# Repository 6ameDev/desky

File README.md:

# desky

Domain-driven monorepo: microcontroller firmware, future cross-platform
client, and shared protocol contracts.

## Repository structure

```plaintext
/
├── .github/              # CI/CD workflows
├── shared/
│   └── protocol/         # Machine-readable contracts, packet schemas, byte maps
├── embedded/             # C++ PlatformIO microcontroller firmware
│   ├── docs/             # documentation & architecture (untracked, owner-managed)
│   ├── scripts/          # UDP drive/telemetry peers (untracked, owner-managed)
│   ├── include/
│   ├── lib/
│   ├── src/
│   ├── test/
│   ├── Makefile
│   └── platformio.ini
├── client/               # Empty placeholder for future KMP / Compose project
├── .gitignore
├── AGENTS.md
└── README.md
```

## Firmware (PlatformIO)

All PlatformIO commands run inside `./embedded`:

```bash
cd embedded && pio run                 # verify compilation (dev)
cd embedded && pio run -e desky-release
cd embedded && pio test -e native-test # host Unity tests, no hardware
```

Prefer `make` targets (they encode the lessons) from the same directory:

```bash
cd embedded && make check        # gate: format + pins + both builds + host tests
cd embedded && make build
cd embedded && make test
cd embedded && make upload-monitor
```

Home WiFi setup (robot joins the home router so the laptop keeps internet):

```bash
cp embedded/.env.example embedded/.env   # fill in DESKY_LINK_SECRET only
```

Flash any firmware, boot with the head linked, then join the robot AP and
store the home credentials in the captive portal. No compiled WiFi secrets.

## Protocol contracts

See `shared/protocol/README.md` for the binary UDP packet layout
(6-byte control, 9-byte telemetry, big-endian, XOR checksum).
Normative source: `embedded/src/middleware/udp_codec.h`.

## Docs

Start at `embedded/docs/architecture/v2.md`, then `AGENTS.md`.
Serial/crash workflow: `embedded/docs/debugging.md`.

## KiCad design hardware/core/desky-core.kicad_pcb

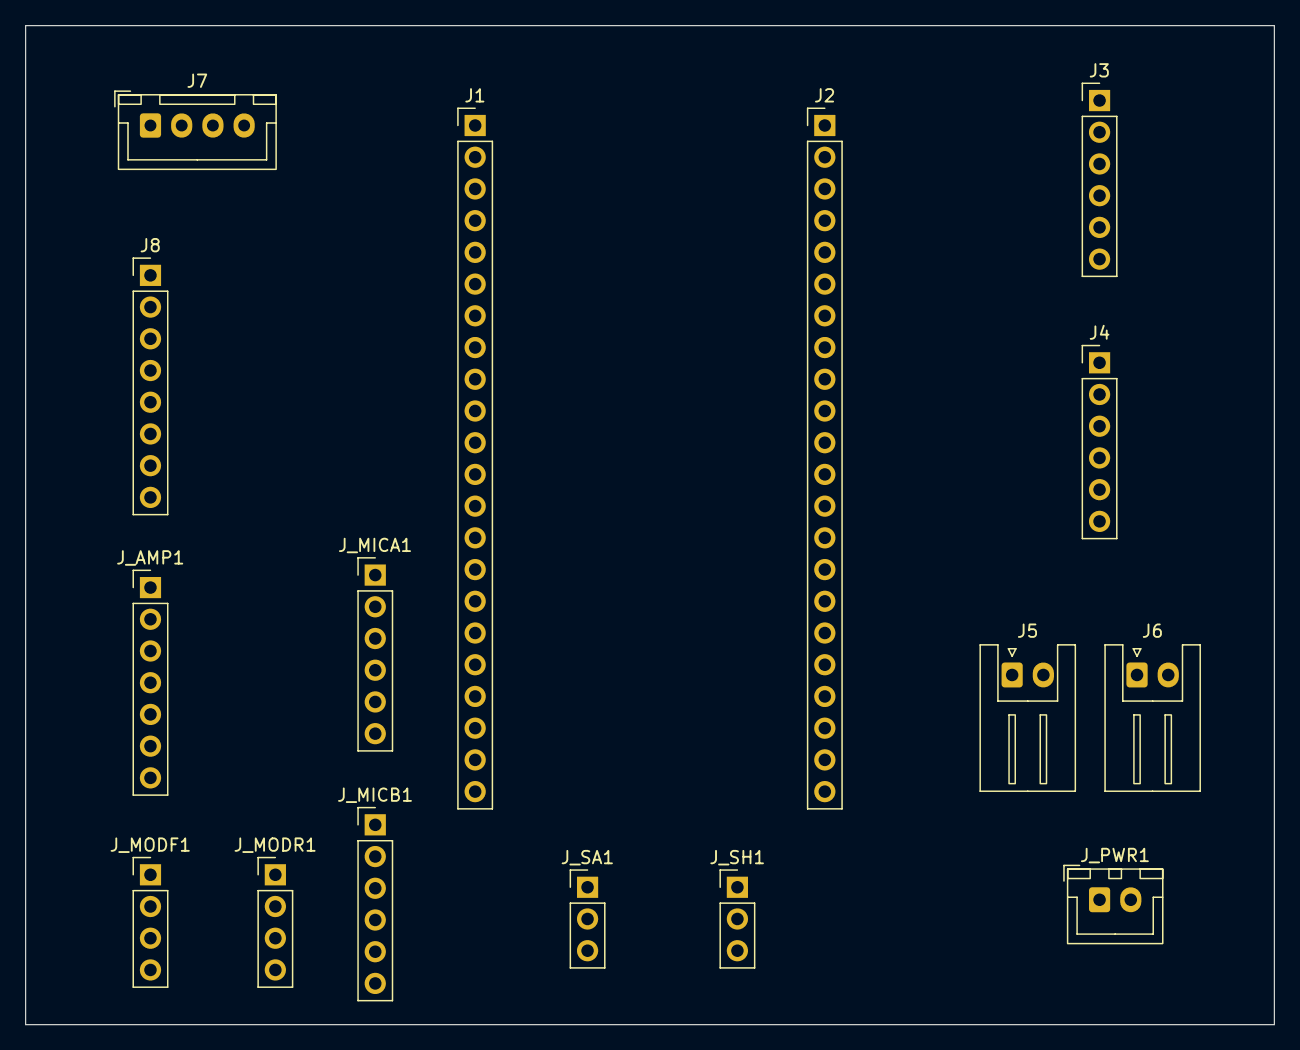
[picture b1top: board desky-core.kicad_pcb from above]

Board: 2 copper layers, 100.0 x 80.0 mm, 16 parts (0 on the bottom side), 24 nets, no tracks yet.

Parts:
J1: S3-LEFT; PinHeader_1x22_P2.54mm_Vertical
J2: S3-RIGHT; PinHeader_1x22_P2.54mm_Vertical
J3: DRV-LOGIC; PinHeader_1x06_P2.54mm_Vertical
J4: DRV-MOTOR; PinHeader_1x06_P2.54mm_Vertical
J5: MOT-L; JST_XH_S2B-XH-A_1x02_P2.50mm_Horizontal
J6: MOT-R; JST_XH_S2B-XH-A_1x02_P2.50mm_Horizontal
J7: TOF-VL53L0X; JST_XH_B4B-XH-A_1x04_P2.50mm_Vertical
J8: MPU-6500; PinHeader_1x08_P2.54mm_Vertical
J_AMP1: AMP-MAX98357A; PinHeader_1x07_P2.54mm_Vertical
J_MICA1: MIC-L; PinHeader_1x06_P2.54mm_Vertical
J_MICB1: MIC-R; PinHeader_1x06_P2.54mm_Vertical
J_MODF1: MOD-FWD-RCPT; PinHeader_1x04_P2.54mm_Vertical
J_MODR1: MOD-REV-RCPT; PinHeader_1x04_P2.54mm_Vertical
J_PWR1: 5V-IN; JST_XH_B2B-XH-A_1x02_P2.50mm_Vertical
J_SA1: SERVO-ARM; PinHeader_1x03_P2.54mm_Vertical
J_SH1: SERVO-HEAD; PinHeader_1x03_P2.54mm_Vertical

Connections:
EMIT_FWD: J1.19, J_MODF1.4
EMIT_REV: J1.20, J_MODR1.4
GND: J1.22, J2.1, J2.21, J2.22, J3.3, J7.2, J8.2, J8.7, J_AMP1.6, J_MICA1.3, J_MICA1.6, J_MICB1.6, J_MODF1.2, J_MODR1.2, J_PWR1.2, J_SA1.3, J_SH1.3
I2C_SCL: J1.17, J7.4, J8.3
I2C_SDA: J1.16, J7.3, J8.4
I2S_BCLK: J1.9, J_AMP1.2, J_MICA1.1, J_MICB1.1
I2S_DIN: J1.11, J_MICA1.4, J_MICB1.4
I2S_DOUT: J1.10, J_AMP1.3
I2S_WS: J1.8, J_AMP1.1, J_MICA1.2, J_MICB1.2
MOT_L1: J4.2, J5.1
MOT_L2: J4.3, J5.2
MOT_R1: J4.4, J6.1
MOT_R2: J4.5, J6.2
M_FAULT: J1.12, J4.6
M_IN1: J1.4, J3.6
M_IN2: J1.5, J3.5
M_IN3: J1.6, J3.2
M_IN4: J1.7, J3.1
SERVO_ARM: J2.6, J_SA1.1
SERVO_HEAD: J2.7, J_SH1.1
TCRT_FWD: J2.4, J_MODF1.3
TCRT_REV: J2.5, J_MODR1.3
VCC_3V3: J1.1, J1.2, J7.1, J8.1, J_MICA1.5, J_MICB1.3, J_MICB1.5, J_MODF1.1, J_MODR1.1
VCC_5V: J1.21, J3.4, J4.1, J_AMP1.7, J_PWR1.1, J_SA1.2, J_SH1.2

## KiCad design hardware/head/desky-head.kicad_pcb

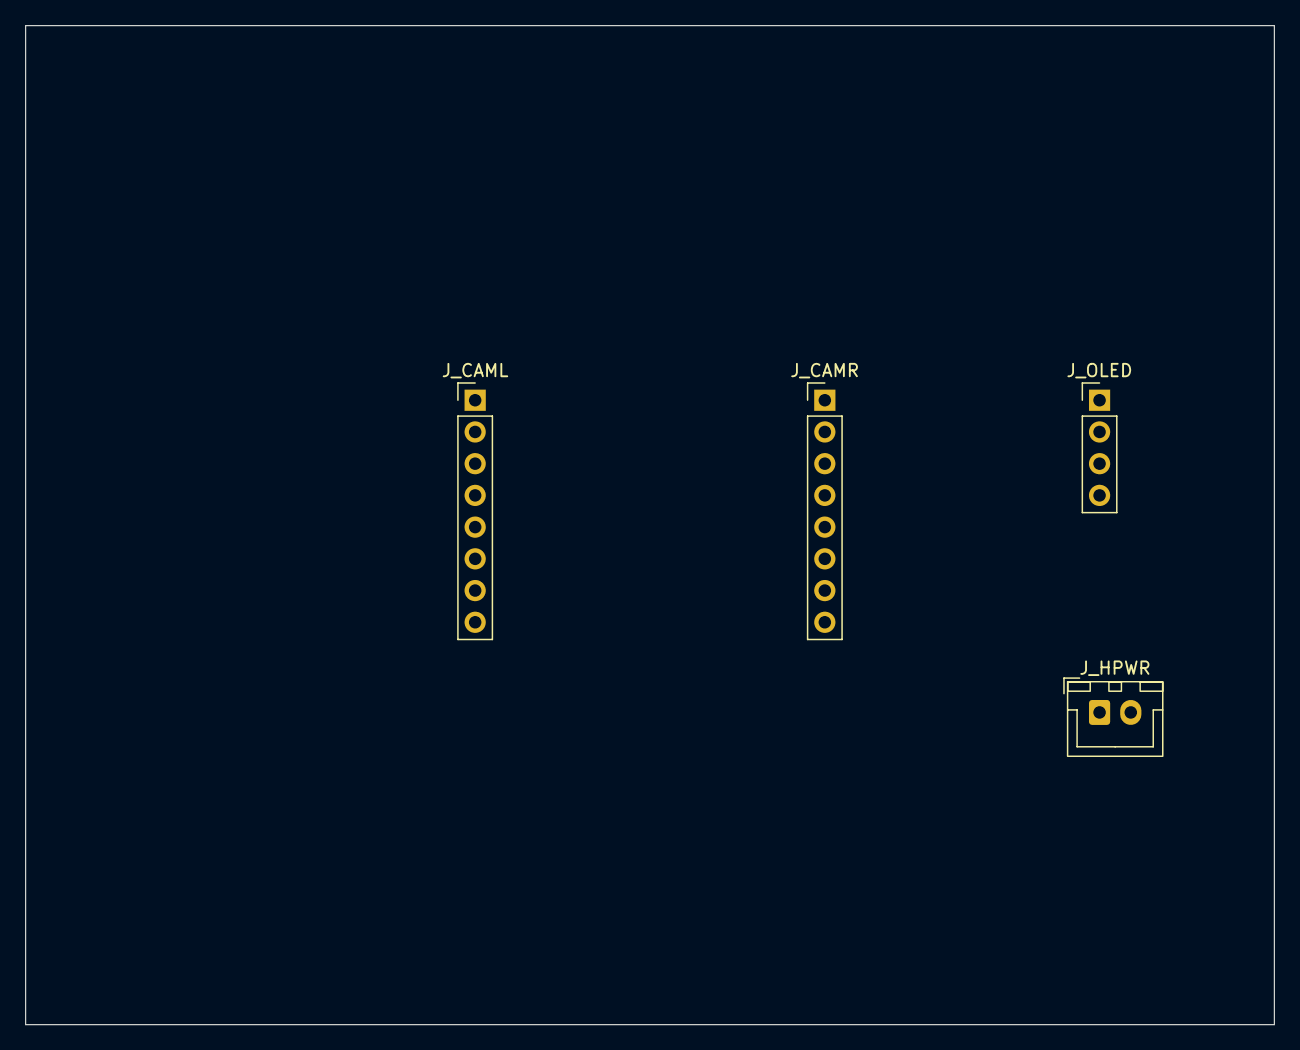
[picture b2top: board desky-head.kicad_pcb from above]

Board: 2 copper layers, 100.0 x 80.0 mm, 4 parts (0 on the bottom side), 5 nets, no tracks yet.

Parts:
J_CAML: CAM-LEFT; PinHeader_1x08_P2.54mm_Vertical
J_CAMR: CAM-RIGHT; PinHeader_1x08_P2.54mm_Vertical
J_HPWR: 5V-IN; JST_XH_B2B-XH-A_1x02_P2.50mm_Vertical
J_OLED: OLED-096; PinHeader_1x04_P2.54mm_Vertical

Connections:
GND: J_CAML.7, J_CAMR.4, J_CAMR.8, J_HPWR.2, J_OLED.1
OLED_SCL: J_CAML.4, J_OLED.3
OLED_SDA: J_CAML.3, J_OLED.4
VCC_3V3: J_CAMR.1, J_OLED.2
VCC_5V: J_CAML.8, J_HPWR.1

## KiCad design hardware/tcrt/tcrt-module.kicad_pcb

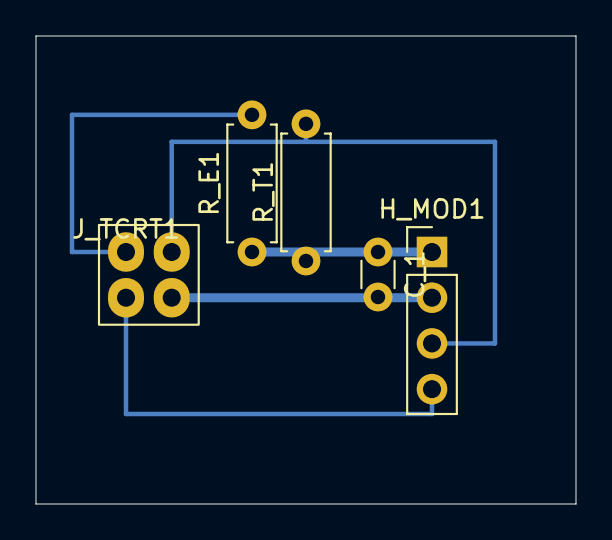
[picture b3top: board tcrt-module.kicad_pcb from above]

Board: 2 copper layers, 30.0 x 26.0 mm, 5 parts (0 on the bottom side), 5 nets.

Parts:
C_1: 100nF; C_Disc_D3.0mm_W1.6mm_P2.50mm
H_MOD1: MOD-4P; PinHeader_1x04_P2.54mm_Vertical
J_TCRT1: TCRT5000; TCRT5000_2x2_P2.54mm
R_E1: 220Ω; R_Axial_DIN0207_L6.3mm_D2.5mm_P7.62mm_Horizontal
R_T1: 10k; R_Axial_DIN0207_L6.3mm_D2.5mm_P7.62mm_Horizontal

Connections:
EA: J_TCRT1.1, R_E1.2
EMIT: H_MOD1.4, J_TCRT1.2
GND: C_1.2, H_MOD1.2, J_TCRT1.4
OUT: H_MOD1.3, J_TCRT1.3, R_T1.2
VCC_3V3: C_1.1, H_MOD1.1, R_E1.1, R_T1.1
